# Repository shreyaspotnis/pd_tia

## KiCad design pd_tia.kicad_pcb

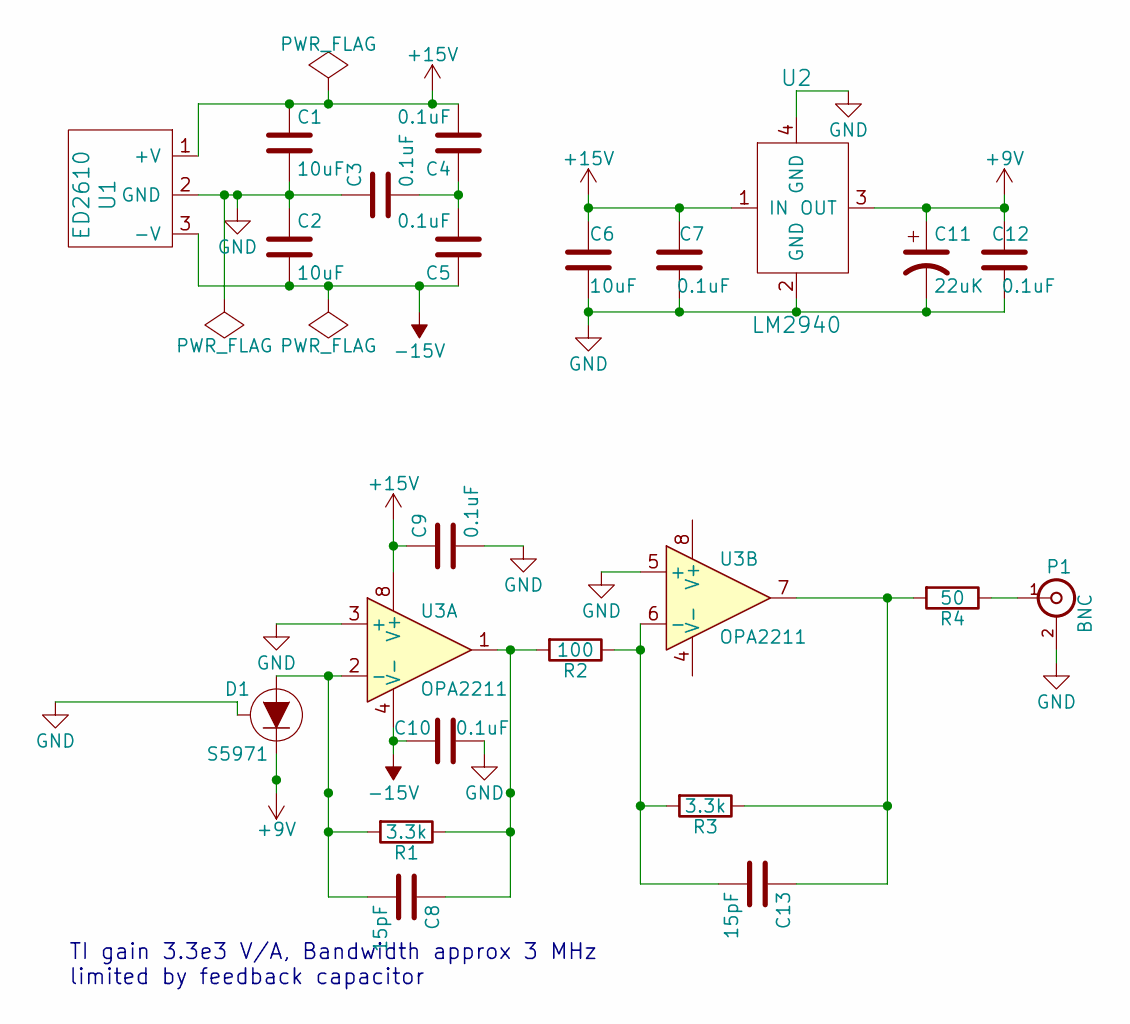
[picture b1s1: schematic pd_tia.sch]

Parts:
C1, C2, C6: 10uF; C_0805_HandSoldering
C3, C4, C5, C7, C9, C10, C12: 0.1uF; C_0805_HandSoldering
C8, C13: 15pF; C_0603_HandSoldering
C11: 22uK; C_2225_HandSoldering
D1: S5971; TO-18-3
P1: BNC; SMA_throughhole
R1, R3: 3.3k; R_0805_HandSoldering
R2: 100; R_0805_HandSoldering
R4: 50; R_0805_HandSoldering
U1: ED2610
U2: LM2940; SOT-223
U3: OPA2211; SOIC-8-1EP_3.9x4.9mm_Pitch1.27mm

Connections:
+9V: C11.1, C12.2, D1.1 (K), U2.3 (OUT)
+15V: C1.1, C4.2, C6.1, C7.2, C9.1, U1.1 (+V), U2.1 (IN), U3.8 (V+)
-15V: C2.2, C5.1, C10.1, U1.3 (-V), U3.4 (V-)
GND: C1.2, C2.1, C3.1, C6.2, C7.1, C9.2, C10.2, C11.2, C12.1, D1.2 (Case), P1.2 (Ext), U1.2 (GND), U2.2 (GND), U2.4 (GND), U3.3 (+), U3.5 (+)
unnamed: C3.2, C4.1, C5.2
unnamed: C8.1, R1.1, R2.2, U3.1
unnamed: C8.2, D1.3 (A), R1.2, U3.2 (-)
unnamed: C13.1, R3.1, R4.2, U3.7
unnamed: C13.2, R2.1, R3.2, U3.6 (-)
unnamed: P1.1 (In), R4.1

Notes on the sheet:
TI gain 3.3e3 V/A, Bandwidth approx 3 MHz limited by feedback capacitor

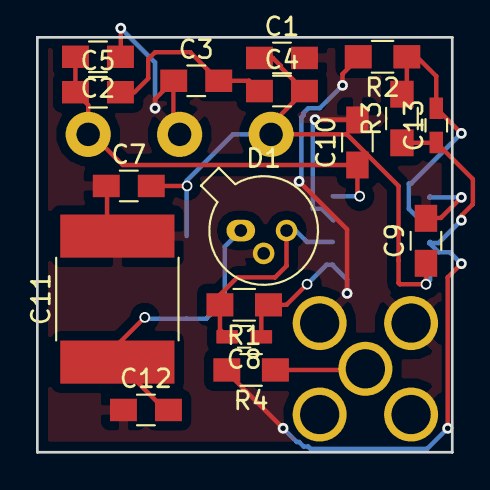
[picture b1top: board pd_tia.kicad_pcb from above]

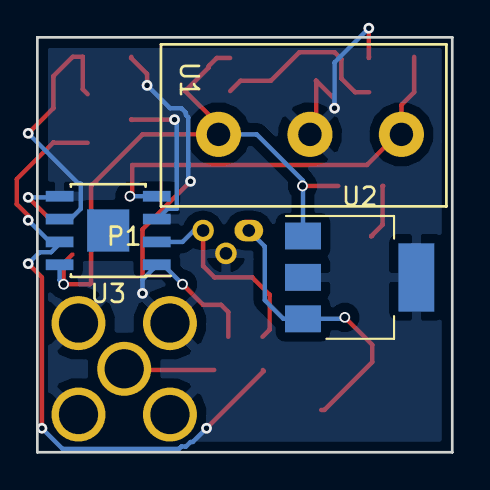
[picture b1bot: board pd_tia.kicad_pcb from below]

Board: 2 copper layers, 23.1 x 23.1 mm, 21 parts (4 on the bottom side), 10 nets.

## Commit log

2017-03-08 :circus_tent: Added .gitattributes & .gitignore files
2017-03-08 Blank project
2017-03-08 Added libraries
2017-03-08 Power supply and regulation done
2017-03-08 Schematic done
2017-03-08 Added footprint for BNC
2017-03-08 Autorouter found a solution, but on a bigger board
2017-03-08 Changed BNC footprint
2017-03-13 Added SMA connector instead of BNC
2017-03-13 First shot at layout... almost all components in
2017-03-13 Almost done. Not quite fitting on board
2017-03-13 More autorouting
